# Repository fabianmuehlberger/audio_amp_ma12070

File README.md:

# AUDIO AMP ma12070/p

## THIS DESIGN IS OUTDATED
currently working cleaning up the schematics and PCB as well as revisiting the power section for improved SNR

PCB for ma12070p Merus IC ref design

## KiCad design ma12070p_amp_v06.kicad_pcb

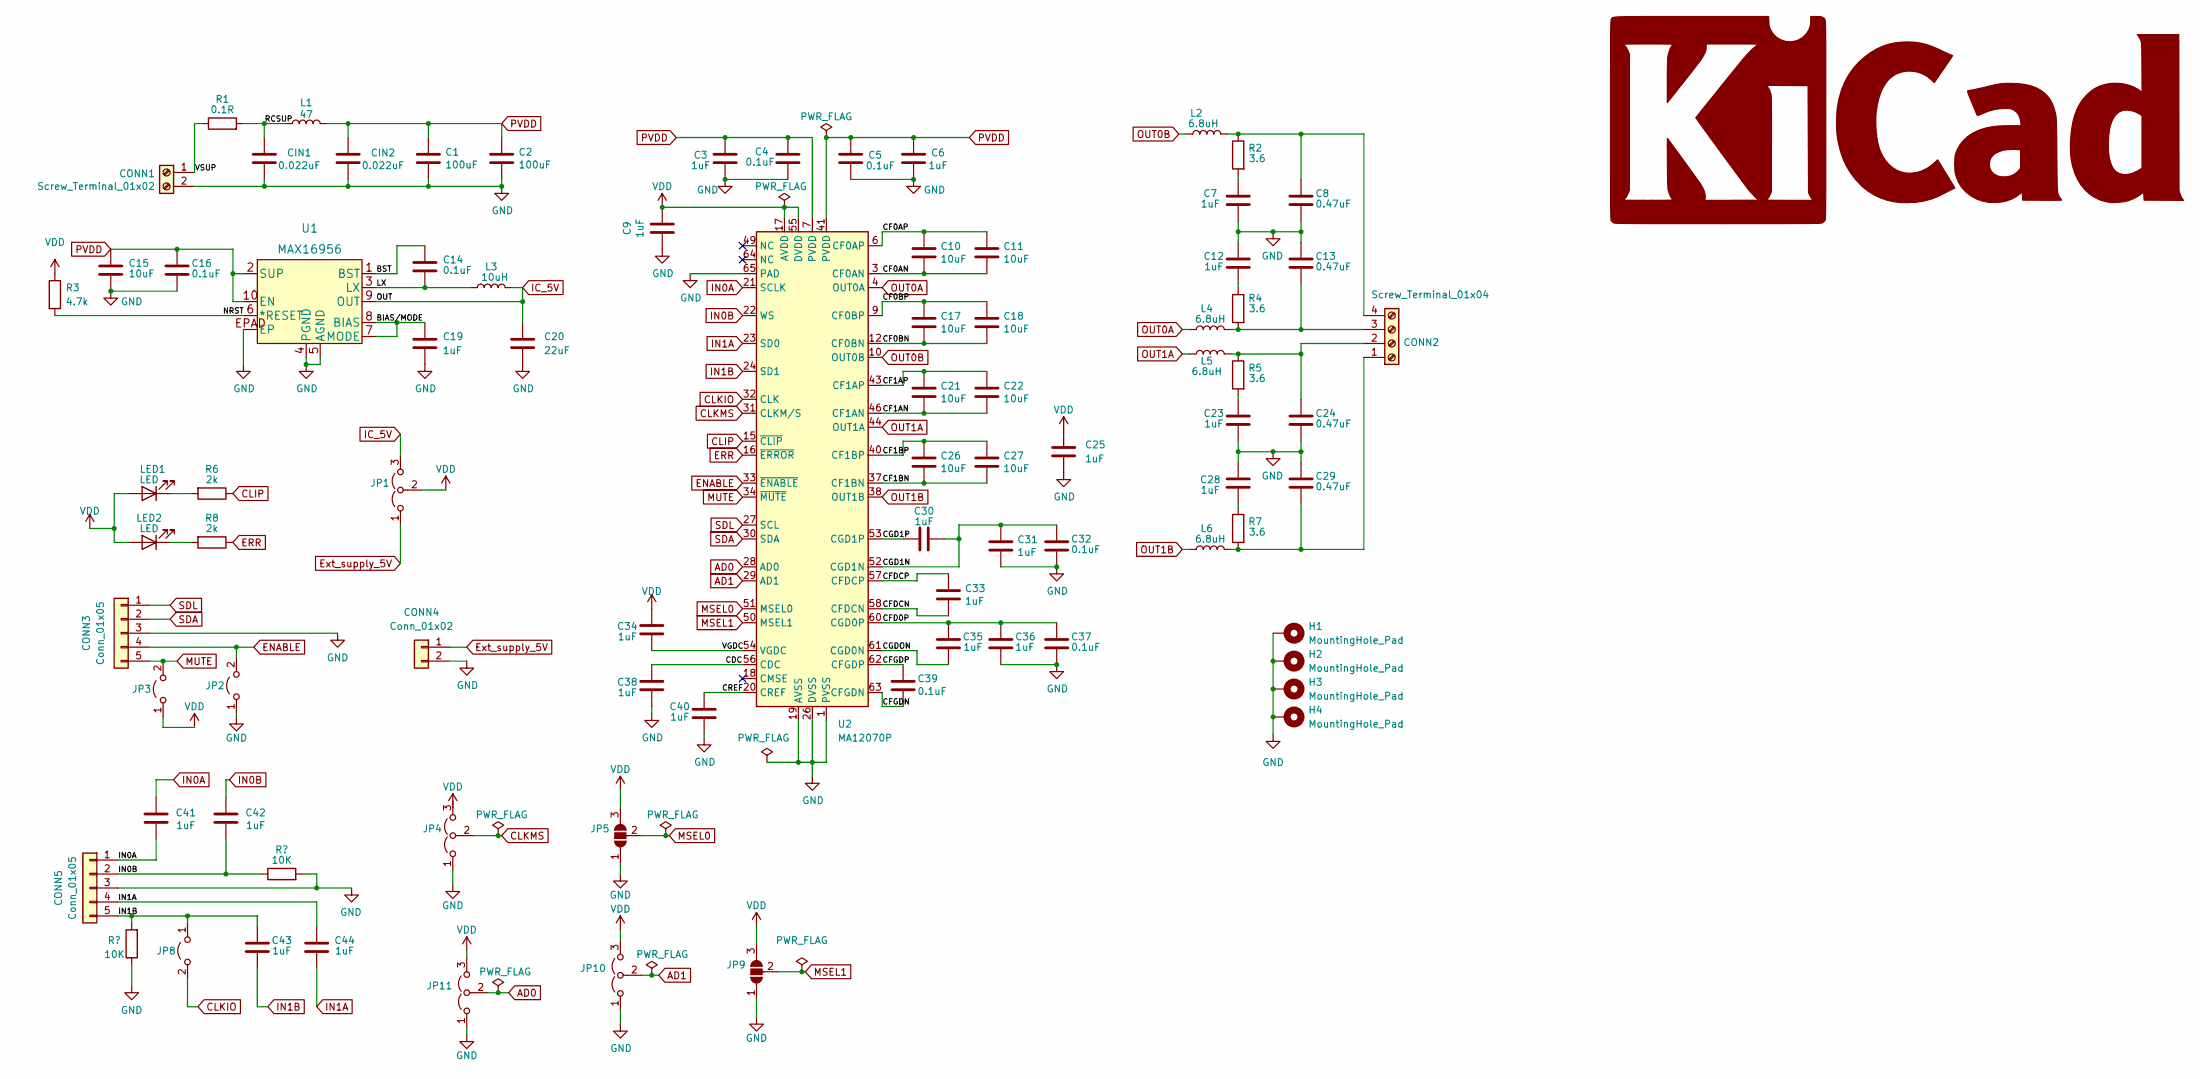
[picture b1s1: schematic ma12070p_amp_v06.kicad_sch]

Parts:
C1, C2: 100uF; CP_Radial_D10.0mm_P5.00mm; DigikeyRef UFG1V101MPM
C3, C6, C9, C19, C25, C30, C31, C33, C34, C35, C36, C38, C40, C41, C42, C43, C44: 1uF; C_1206_3216Metric
C4, C5, C14, C16, C32, C37, C39: 0.1uF; C_1206_3216Metric
C7, C12, C23, C28: 1uF; C_Rect_L7.3_W4.5_P5.0
C8, C13, C24, C29: 0.47uF; C_Rect_L7.3_W4.5_P5.0
C10, C11, C15, C17, C18, C21, C22, C26, C27: 10uF; C_1206_3216Metric
C20: 22uF; C_1206_3216Metric
CIN1, CIN2: 0.022uF; C_1206_3216Metric
CONN1: Screw_Terminal_01x02; TerminalBlock_Phoenix_MKDS-1,5-2_1x02_P5.00mm_Horizontal
CONN2: Screw_Terminal_01x04; TerminalBlock_Phoenix_MKDS-1,5-4_1x04_P5.00mm_Horizontal
CONN3, CONN5: Conn_01x05; PinHeader_1x05_P2.54mm_Vertical
CONN4: Conn_01x02; PinHeader_1x02_P2.54mm_Vertical
H1, H2, H3, H4: MountingHole_Pad; MountingHole_4mm_Pad
JP1, JP11: SolderJumper_3_Open; PinHeader_1x03_P2.54mm_Vertical
JP2, JP3, JP8: SolderJumper_2_Open; PinHeader_1x02_P2.54mm_Vertical
JP4, JP10: Jumper:Jumper_3_Open; PinHeader_1x03_P2.54mm_Vertical
JP5, JP9: SolderJumper_3_Open; SolderJumper-3_P1.3mm_Open_Pad1.0x1.5mm
L1: 47; L_2010_5025Metric
L2, L4, L5, L6: 6.8uH; L_Radial_TH_Murata_D16.9_P14.0
L3: 10uH; RLB0712-100KL
LED1, LED2: LED; LED_1206_3216Metric
R1: 0.1R; R_2512_6332Metric
R2, R4, R5, R7: 3.6; R_1206_3216Metric
R3: 4.7k; R_1206_3216Metric
R6, R8: 2k; R_1206_3216Metric
U1: MAX16956; MAX16956AUBD&slash_V&plus_
U2: MA12070P; QFN-64-1EP_9x9mm_P0.5mm_EP5.45x5.45mm

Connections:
/BIAS/MODE: C19.1, U1.7 (MODE), U1.8 (BIAS)
/BST: C14.1, U1.1 (BST)
/CDC: C38.1, U2.56 (CDC)
/CF0AN: C10.2, C11.2, U2.3 (CF0AN)
/CF0AP: C10.1, C11.1, U2.6 (CF0AP)
/CF0BN: C17.2, C18.2, U2.12 (CF0BN)
/CF0BP: C17.1, C18.1, U2.9 (CF0BP)
/CF1AN: C21.2, C22.2, U2.46 (CF1AN)
/CF1AP: C21.1, C22.1, U2.43 (CF1AP)
/CF1BN: C26.2, C27.2, U2.37 (CF1BN)
/CF1BP: C26.1, C27.1, U2.40 (CF1BP)
/CFD0P: C35.1, C36.1, C37.2, U2.60 (CGD0P)
/CFDCN: C33.2, U2.58 (CFDCN)
/CFDCP: C33.1, U2.57 (CFDCP)
/CFGDN: C39.1, U2.63 (CFGDN)
/CFGDP: C39.2, U2.62 (CFGDP)
/CGD1N: C30.1, C31.1, C32.2, U2.52 (CGD1N)
/CGD1P: C30.2, U2.53 (CGD1P)
/CGDON: C35.2, U2.61 (CGD0N)
/CREF: C40.1, U2.20 (CREF)
/LX: C14.2, L3.1, U1.3 (LX)
/NRST: R3.2, U1.6 (*RESET)
/RCSUP: CIN1.2, L1.1, R1.2
/VGDC: C34.2, U2.54 (VGDC)
/VSUP: CONN1.1, R1.1
AD0: JP11.2 (C), U2.28 (AD0)
AD1: JP10.2 (C), U2.29 (AD1)
CLIP: R6.1, U2.15 (~CLIP)
CLKIO: JP8.2 (B), U2.32 (CLK)
CLKMS: JP4.2 (C), U2.31 (CLKM/S)
ENABLE: CONN3.4, JP2.2 (B), U2.33 (~ENABLE)
ERR: R8.1, U2.16 (~ERROR)
Ext_supply_5V: CONN4.1, JP1.1 (A)
GND: C1.2, C2.2, C3.2, C4.2, C5.2, C6.2, C7.2, C8.1, C9.2, C12.2, C13.2, C15.2, C16.2, C19.2, C20.2, C23.2, C24.1, C25.2, C28.2, C29.2, C31.2, C32.1, C36.2, C37.1, C38.2, C40.2, CIN1.1, CIN2.1, CONN1.2, CONN3.3, CONN4.2, CONN5.3, H1.1, H2.1, H3.1, H4.1, JP2.1 (A), JP4.1 (A), JP5.1 (A), JP9.1 (A), JP10.1 (A), JP11.1 (A), U1.4 (PGND), U1.5 (AGND), U1.EPAD (EP), U2.1 (PVSS), U2.2 (PVSS), U2.13 (PVSS), U2.14 (PVSS), U2.19 (AVSS), U2.25 (AVSS), U2.26 (DVSS), U2.35 (PVSS), U2.36 (PVSS), U2.47 (PVSS), U2.48 (PVSS), U2.59 (DVSS), U2.65 (PAD); also elsewhere on the board
IC_5V: C20.1, JP1.3 (B), L3.2, U1.9 (OUT)
IN0A: C41.1, C41.2, CONN5.1, U2.21 (SCLK)
IN0B: C42.1, C42.2, CONN5.2, U2.22 (WS); also elsewhere on the board
IN1A: C44.1, C44.2, CONN5.4, U2.23 (SD0)
IN1B: C43.1, C43.2, CONN5.5, JP8.1 (A), U2.24 (SD1); also elsewhere on the board
MSEL0: JP5.2 (C), U2.51 (MSEL0)
MSEL1: JP9.2 (C), U2.50 (MSEL1)
MUTE: CONN3.5, JP3.2 (B), U2.34 (~MUTE)
unnamed: C7.1, R2.2
unnamed: C8.2, CONN2.4, L2.1, R2.1
unnamed: C12.1, R4.1
unnamed: C13.1, CONN2.3, L4.1, R4.2
unnamed: C23.1, R5.2
unnamed: C24.2, CONN2.2, L5.1, R5.1
unnamed: C28.1, R7.1
unnamed: C29.1, CONN2.1, L6.1, R7.2
unnamed: LED1.1 (K), R6.2
unnamed: LED2.1 (K), R8.2
OUT0A: L4.2, U2.4 (OUT0A), U2.5 (OUT0A)
OUT0B: L2.2, U2.10 (OUT0B), U2.11 (OUT0B)
OUT1A: L5.2, U2.44 (OUT1A), U2.45 (OUT1A)
OUT1B: L6.2, U2.38 (OUT1B), U2.39 (OUT1B)
PVDD: C1.1, C2.1, C3.1, C4.1, C5.1, C6.1, C15.1, C16.1, CIN2.2, L1.2, U1.2 (SUP), U1.10 (EN), U2.7 (PVDD), U2.8 (PVDD), U2.41 (PVDD), U2.42 (PVDD)
SDA: CONN3.2, U2.30 (SDA)
SDL: CONN3.1, U2.27 (SCL)
VDD: C9.1, C25.1, C34.1, JP1.2 (C), JP3.1 (A), JP5.3 (B), JP9.3 (B), JP10.3 (B), JP11.3 (B), LED1.2 (A), LED2.2 (A), R3.1, U2.17 (AVDD), U2.55 (DVDD)

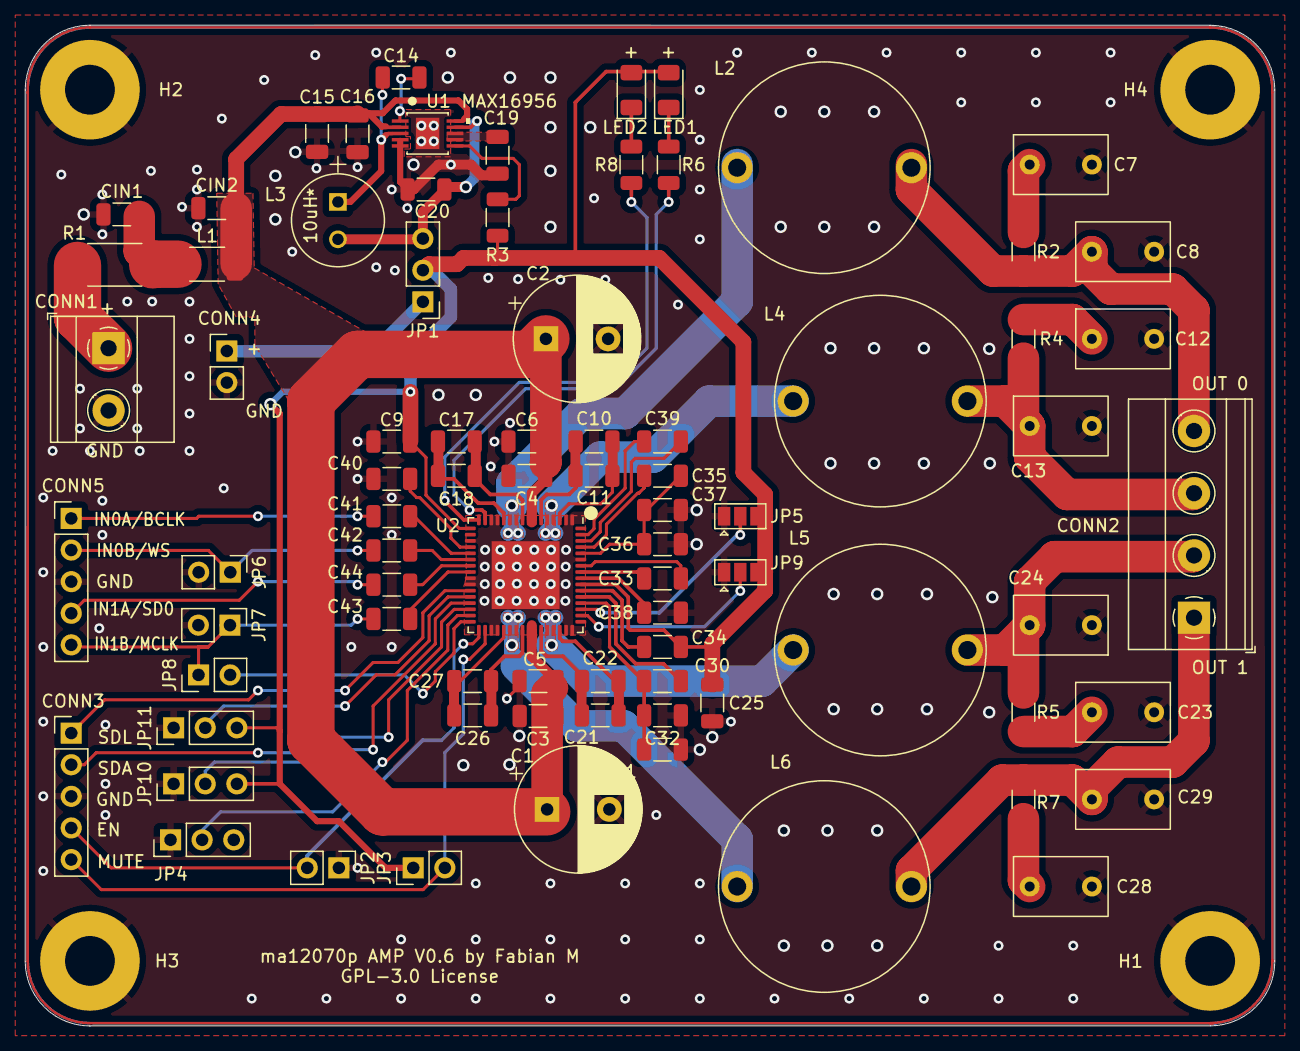
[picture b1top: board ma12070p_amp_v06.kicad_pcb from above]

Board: 2 copper layers, 100.4 x 80.4 mm, 84 parts (0 on the bottom side), 60 nets.

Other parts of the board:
JP6, JP7: SolderJumper_2_Open; PinHeader_1x02_P2.54mm_Vertical

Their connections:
GND: JP6.2 (B), JP7.2 (B); also elsewhere on the board
IN0B: JP6.1 (A); also elsewhere on the board
IN1B: JP7.1 (A); also elsewhere on the board

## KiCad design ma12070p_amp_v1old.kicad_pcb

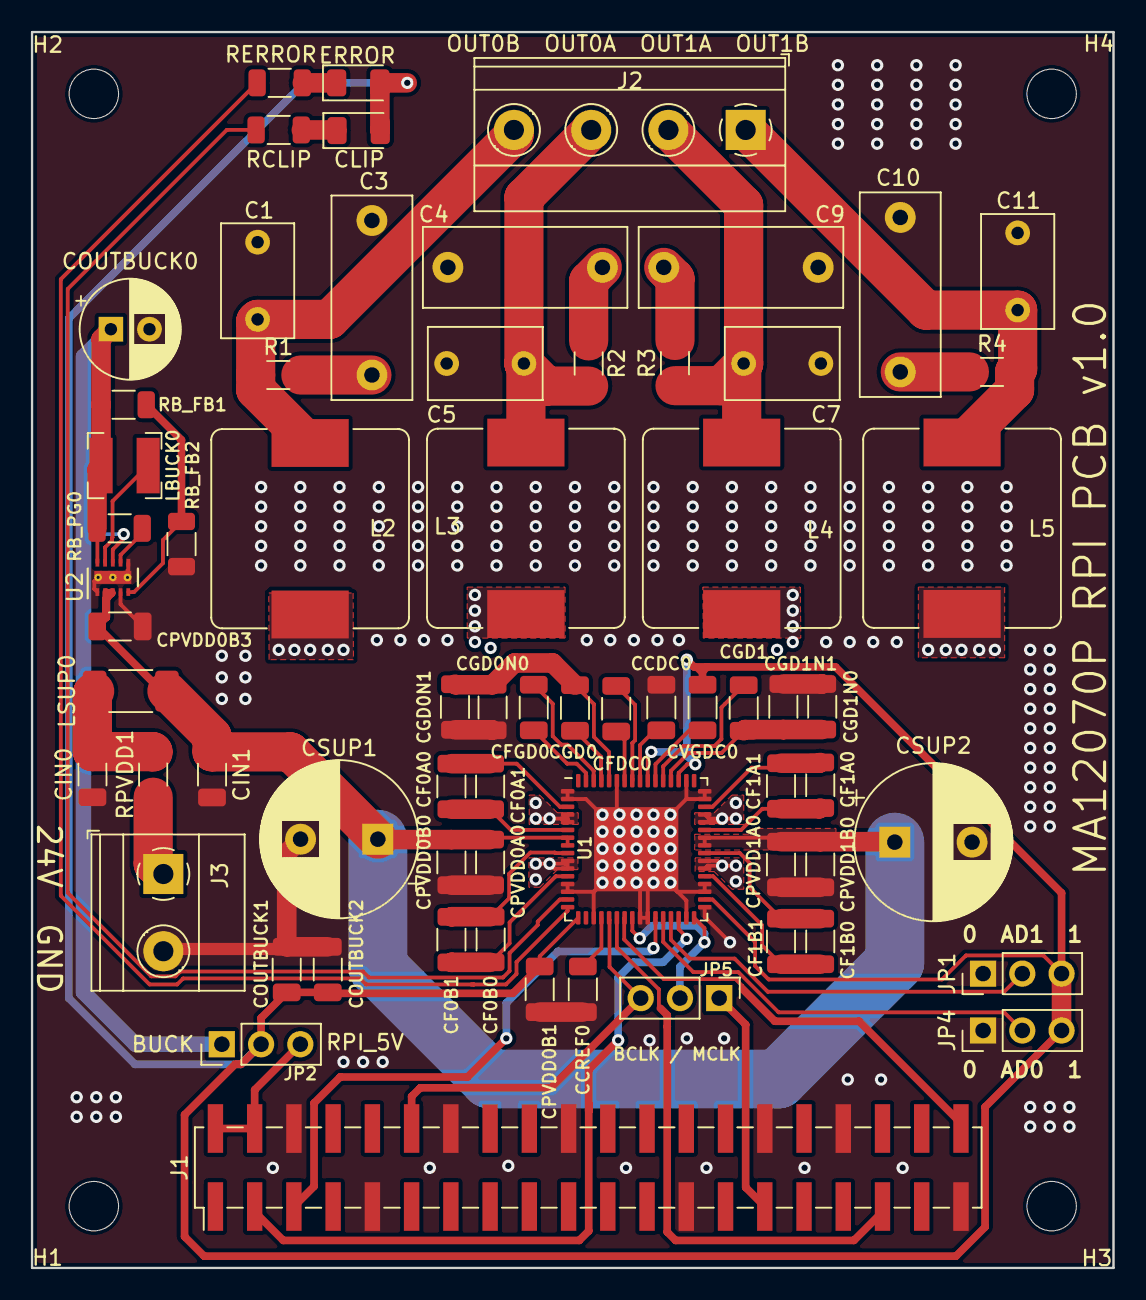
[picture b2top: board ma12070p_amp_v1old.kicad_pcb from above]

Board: 2 copper layers, 70.0 x 80.0 mm, 71 parts (0 on the bottom side), 54 nets.

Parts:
C1, C5, C7, C11: 0.47uF; C_Rect_L7.2mm_W4.5mm_P5.00mm_FKS2_FKP2_MKS2_MKP2
C3, C4, C9, C10: 1uF; C_Rect_L13.0mm_W5.0mm_P10.00mm_FKS3_FKP3_MKS4
CCDC0: 1uF; C_1206_3216Metric
CCREF0: 1uF; C_1206_3216Metric
CF0A0, CF0A1, CF0B0, CF0B1, CF1A0, CF1A1, CF1B0, CF1B1: 10uF; C_1206_3216Metric
CFDC0: 1uF; C_1206_3216Metric
CFGD0: 0.1uF; C_1206_3216Metric
CGD0, CGD0N1, CGD1, CGD1N1: 1uF; C_1206_3216Metric
CGD0N0, CGD1N0: 0.1uF; C_1206_3216Metric
CIN0, CIN1: 22nF; C_1206_3216Metric
CLIP: LED; LED_1206_3216Metric
COUTBUCK0: 22uF; CP_Radial_D6.3mm_P2.50mm
COUTBUCK1: 1uF; C_1206_3216Metric
COUTBUCK2: 0.1uF; C_1206_3216Metric
CPVDD0A0, CPVDD1A0: 0.1uF; C_1206_3216Metric
CPVDD0B0, CPVDD0B1, CPVDD0B3, CPVDD1B0: 1uF; C_1206_3216Metric
CSUP1, CSUP2: 330uF/35V; CP_Radial_D10.0mm_P5.00mm
CVGDC0: 1uF; C_1206_3216Metric
ERROR: LED; LED_1206_3216Metric
H1, H2, H3, H4: MountingHole; MountingHole_3.2mm_M3
J1: RPI_GPIO; PinHeader_2x20_P2.54mm_Vertical_SMD
J2: Screw_Terminal_01x04; TerminalBlock_Phoenix_MKDS-1,5-4_1x04_P5.00mm_Horizontal
J3: Screw_Terminal_01x02; TerminalBlock_Phoenix_MKDS-1,5-2_1x02_P5.00mm_Horizontal
JP1, JP2, JP4, JP5: Jumper_3_Open; PinHeader_1x03_P2.54mm_Vertical
L2, L3, L4, L5: 3.3uH; L_Bourns_SRP1245A
LBUCK0: SRN4026-100M; L_Bourns-SRN4018
LSUP0: Ferrite 2743019447; L_2010_5025Metric_Pad1.52x2.65mm_HandSolder
R1, R2, R3, R4: 3.6; R_1206_3216Metric
RB_FB1: 1M; R_1206_3216Metric
RB_FB2: 383k; R_1206_3216Metric
RB_PG0: 100k; R_1206_3216Metric
RCLIP: 2k; R_1206_3216Metric
RERROR: 2k; R_1206_3216Metric
RPVDD1: 0.1R; R_1206_3216Metric
U1: MA12070P; QFN-64-1EP_9x9mm_P0.5mm_EP5.45x5.45mm
U2: TPS62175DQC; WSON-10-1EP_2x3mm_P0.5mm_EP0.84x2.4mm_ThermalVias

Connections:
/AD0: JP4.2, U1.28
/AD1: JP1.2, U1.29
/BUCK_5V: COUTBUCK0.1, JP2.1, LBUCK0.1, RB_FB1.2, RB_PG0.2, U2.8, U2.10
/CLIP: RCLIP.1, U1.15
/ERROR: RERROR.1, U1.16
/KALI_I2S_MCLK: J1.29, JP5.1
/OUT0A: L3.2, U1.4, U1.5
/OUT0B: L2.2, U1.10, U1.11
/OUT1A: L4.2, U1.44, U1.45
/OUT1B: L5.2, U1.38, U1.39
/PVDD: CIN1.2, CPVDD0A0.1, CPVDD0B0.1, CPVDD0B3.1, CPVDD1A0.1, CPVDD1B0.1, CSUP1.1, CSUP2.1, LSUP0.1, U1.7, U1.8, U1.41, U1.42, U2.2, U2.3
/RPI_5V: J1.2, J1.4, JP2.3
/RPI_I2C_SCL: J1.5, U1.27
/RPI_I2C_SDA: J1.3, U1.30
/RPI_I2S_BCLK: J1.12, JP5.3, U1.21
/RPI_I2S_DATA: J1.40, U1.23
/RPI_I2S_WS: J1.35, U1.22
/VDD: CLIP.2, COUTBUCK1.2, COUTBUCK2.2, CPVDD0B1.1, CVGDC0.2, ERROR.2, JP1.3, JP2.2, JP4.3, U1.17, U1.34, U1.51, U1.55
GND: C1.1, C3.1, C4.2, C5.2, C7.1, C9.1, C10.2, C11.2, CCDC0.2, CCREF0.2, CGD0N0.1, CGD0N1.2, CGD1N0.1, CGD1N1.2, CIN0.1, CIN1.1, COUTBUCK0.2, COUTBUCK1.1, COUTBUCK2.1, CPVDD0A0.2, CPVDD0B0.2, CPVDD0B1.2, CPVDD0B3.2, CPVDD1A0.2, CPVDD1B0.2, CSUP1.2, CSUP2.2, J1.6, J1.9, J1.14, J1.20, J1.25, J1.30, J1.34, J1.39, J3.2, JP1.1, JP4.1, RB_FB2.1, U1.1, U1.2, U1.13, U1.14, U1.19, U1.25, U1.26, U1.31, U1.33, U1.35, U1.36, U1.47, U1.48, U1.50, U1.59, U1.65, U2.1, U2.4, U2.6, U2.11
unnamed: C1.2, J2.4, L2.1, R1.1
unnamed: C3.2, R1.2
unnamed: C4.1, R2.1
unnamed: C5.1, J2.3, L3.1, R2.2
unnamed: C7.2, J2.2, L4.1, R3.1
unnamed: C9.2, R3.2
unnamed: C10.1, R4.1
unnamed: C11.1, J2.1, L5.1, R4.2
unnamed: CCDC0.1, U1.56
unnamed: CCREF0.1, U1.20
unnamed: CF0A0.1, CF0A1.1, U1.6
unnamed: CF0A0.2, CF0A1.2, U1.3
unnamed: CF0B0.1, CF0B1.1, U1.9
unnamed: CF0B0.2, CF0B1.2, U1.12
unnamed: CF1A0.1, CF1A1.1, U1.43
unnamed: CF1A0.2, CF1A1.2, U1.46
unnamed: CF1B0.1, CF1B1.1, U1.40
unnamed: CF1B0.2, CF1B1.2, U1.37
unnamed: CFDC0.1, U1.57
unnamed: CFDC0.2, U1.58
unnamed: CFGD0.1, U1.63
unnamed: CFGD0.2, U1.62
unnamed: CGD0.1, CGD0N0.2, CGD0N1.1, U1.60
unnamed: CGD0.2, U1.61
unnamed: CGD1.1, CGD1N0.2, CGD1N1.1, U1.52
unnamed: CGD1.2, U1.53
unnamed: CIN0.2, LSUP0.2, RPVDD1.2
unnamed: CLIP.1, RCLIP.2
unnamed: CVGDC0.1, U1.54
unnamed: ERROR.1, RERROR.2
unnamed: J3.1, RPVDD1.1
unnamed: JP5.2, U1.24, U1.32
unnamed: LBUCK0.2, U2.9
unnamed: RB_FB1.1, RB_FB2.2, U2.5
unnamed: RB_PG0.1, U2.7

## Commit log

2021-12-08 added project
2021-12-11 small updates to pcb
2021-12-21 change
2021-12-21 Revert "update"
    This reverts commit 23222dc2ff684dbeb0c499af5827ef2ca36430f4.
2021-12-21 Revert "update"
    This reverts commit 6da7eb9e9a8a0503f4a45a80096061478bca19da.
2021-12-21 Revert "Merge branch 'main' of https://github.com/fabianmuehlberger/ma12070p_amp_kicad"
    This reverts commit afd773a9720c15933af275e3fcdef7eeb23b86f2, reversing
    changes made to a492eb96612e67492a35cba3f1296495fc6c8237.
2021-12-21 update again
2021-12-22 V0.1
2021-12-22 finished DRC
2021-12-22 minor Changes Vias
2021-12-22 updated some components
2021-12-22 minor update to paths
2021-12-22 changed output Vias
2021-12-27 changed output filter inductors
2021-12-27 changed pictures
2021-12-27 minor changes and cleanup
2021-12-27 made d3 Models for inductors
2021-12-28 fixed issues with locked vias
2021-12-29 layout change of power supp
2021-12-29 return current improvements
2021-12-29 schematic optimizing
2022-01-03 minor improvements on the pcb
2022-01-04 minor improvements, again
2022-01-04 changed via sizes
2022-01-05 moved pvdd lanes - v06
2022-01-05 minor changes
2022-01-05 added datasheets of critical components
2022-01-05 filename cleanup
2022-01-05 cleanup
2022-01-08 updated dcdc converter
2022-01-08 miror improvements and calculation voltage regulator
2022-01-08 minor change
2022-01-08 created gerber
2022-01-08 small change in pcb
2022-01-09 calculation of max16956 jupyter
2022-01-09 Fixed VDD traces
2022-01-10 updated footprints
2022-01-10 DRC Check
2022-01-10 redo of DRC because of mistake
2022-01-10 added kicad logo to board
2022-01-29 working on v0.7

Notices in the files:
ma12070p_amp_v06.kicad_pcb:
GPL-3.0 License
parts and their libraries:
Copyright 2021 Accelerated Designs. All rights reserved.
